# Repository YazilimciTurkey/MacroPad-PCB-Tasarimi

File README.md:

Projeme sponsor oldukları için @PCBWay tekrardan teşekkürler.
PCBWay 10 tanesi 5$ PCB kartlarınızı ürettirebilirsiniz. 
PCBWay size her türlü 3D, CNC, kalıp plastik, ve metal işleme gibi ihtiyaçlarınızı karşılar. 
PCBWay: https://www.pcbway.com/
Tasarım Dosyaları: Yapımda!!
PCBWay detaylı sipariş verme videosu: Yakında!!!
Daha fazla projem için: 
Hackster.io profilim: https://www.hackster.io/hamzadenizyilmaz
#pcbway #pcb #pcbuild 
English/İngilizce
Thanks again @PCBWay for sponsoring my project.
PCBWay You can have your PCB boards produced for 10$. And it provides all kinds of printing and assembly services.
PCBWay: https://www.pcbway.com/
Design Files: Under Construction!!
For more of my projects:
My Hackster.io profile: https://www.hackster.io/hamzadenizyilmaz
#pcbway #pcb #pcbuild #pcbtoday
Videom:https://youtu.be/eG-ILG9O8ic
My video: https://youtu.be/eG-ILG9O8ic

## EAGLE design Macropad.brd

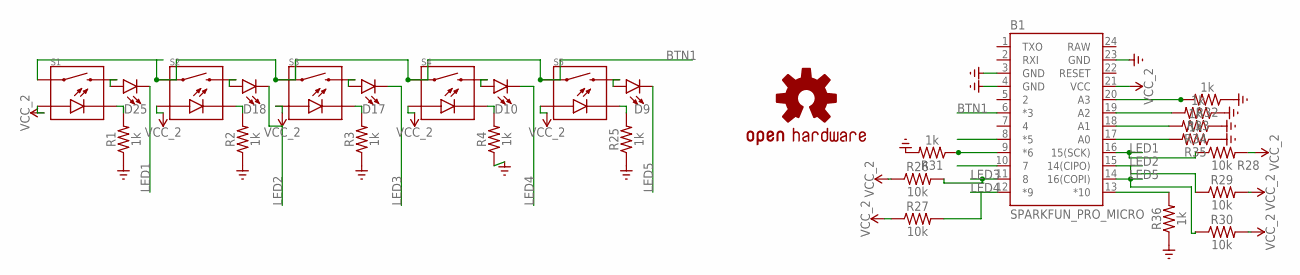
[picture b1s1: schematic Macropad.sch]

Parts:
B1: SPARKFUN_PRO_MICRO
D9, D10, D17, D18, D25: LED3MM; LED_3MM
LOGO1: OSHW-LOGOM-COPPER; OSHW-LOGO-M_COPPER
R1, R2, R3, R4, R25, R31, R32, R33, R34, R35, R36: 1k; AXIAL-0.3
R26, R27, R28, R29, R30: 10k; AXIAL-0.3
S1, S2, S3, S4, S5: 1POLE-FIXPINS-W/LED; 1POLE-FIXPINS-W/LED-EASYSOLDER

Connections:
BTN1: B1.6 (*3), S1.1, S2.1, S3.1, S4.1, S5.1
GND: B1.3 (GND), B1.4 (GND), B1.23 (GND), R1.P$1 (1), R2.P$1 (1), R3.P$1 (1), R4.P$1 (1), R25.P$1 (1), R31.P$2 (2), R32.P$1 (1), R33.P$1 (1), R34.P$1 (1), R35.P$1 (1), R36.P$1 (1)
LED1: B1.16 (15(SCK)), D25.K (C), R28.P$1 (1)
LED2: B1.15 (14(CIPO)), D18.K (C), R29.P$1 (1)
LED3: B1.11 (8), D17.K (C), R26.P$2 (2)
LED4: B1.12 (*9), D10.K (C), R27.P$2 (2)
LED5: B1.14 (16(COPI)), D9.K (C), R30.P$1 (1)
unnamed: R1.P$2 (2), S1.4
unnamed: R2.P$2 (2), S2.4
unnamed: R3.P$2 (2), S3.4
unnamed: R4.P$2 (2), S4.4
unnamed: R25.P$2 (2), S5.4
unnamed: D25.A, S1.2
unnamed: D18.A, S2.2
unnamed: D17.A, S3.2
unnamed: D10.A, S4.2
unnamed: D9.A, S5.2
unnamed: B1.9 (*6), R31.P$1 (1)
unnamed: B1.20 (A3), R32.P$2 (2)
unnamed: B1.19 (A2), R33.P$2 (2)
unnamed: B1.18 (A1), R34.P$2 (2)
unnamed: B1.17 (A0), R35.P$2 (2)
unnamed: B1.13 (*10), R36.P$2 (2)
NET,: B1.8 (*5)
RAW: B1.24 (RAW)
VCC_2: B1.21 (VCC), R26.P$1 (1), R27.P$1 (1), R28.P$2 (2), R29.P$2 (2), R30.P$2 (2), S1.3, S2.3, S3.3, S4.3, S5.3

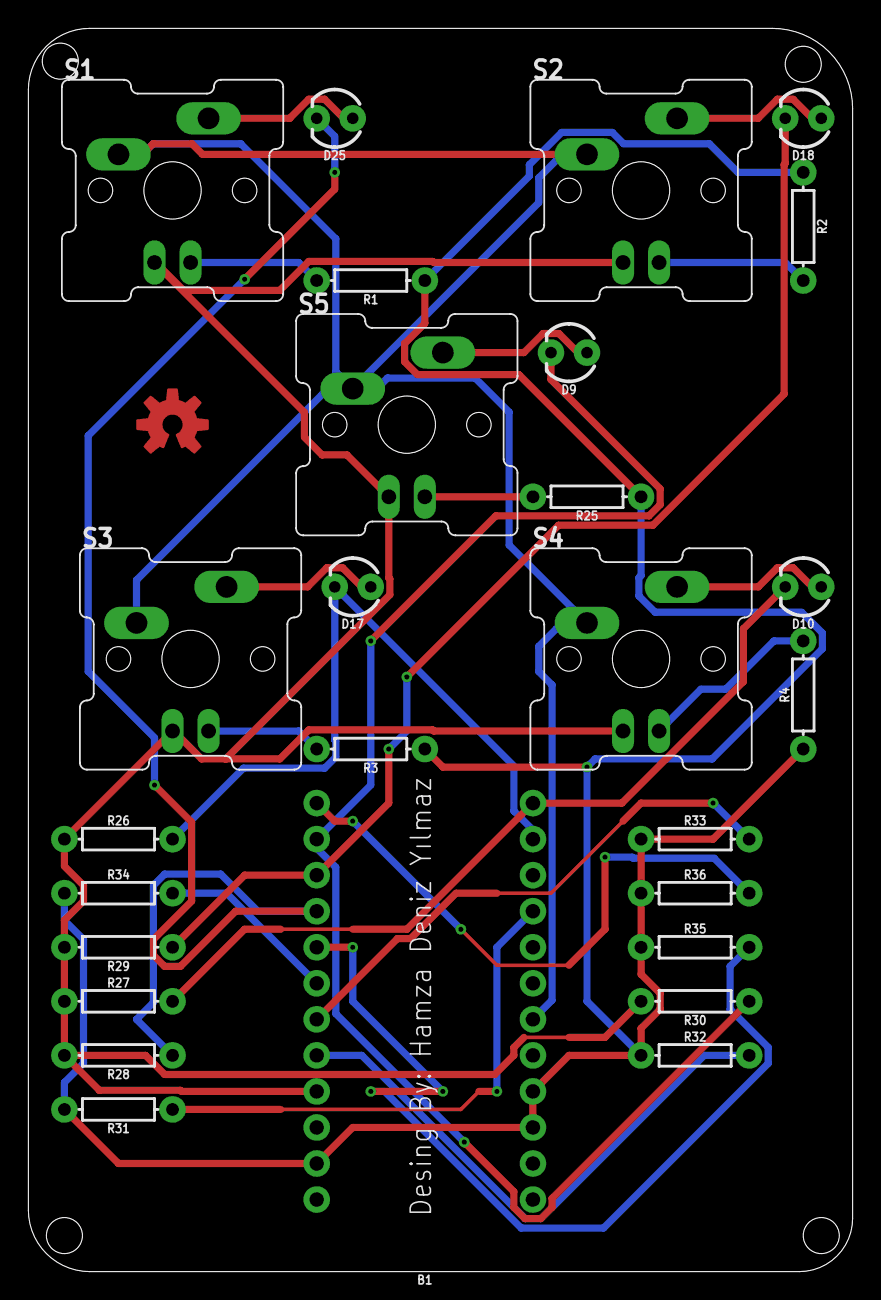
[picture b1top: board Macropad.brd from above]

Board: 2 copper layers, 58.1 x 87.6 mm, 28 parts (0 on the bottom side), 24 nets.

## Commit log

2023-01-13 Macropad.brd
    Macropad.brd
2023-01-13 Macropad.sch
    Macropad.sch

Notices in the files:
parts and their libraries:
SparkFun-Boards: Licensing: Creative Commons ShareAlike 4.0 International - https://creativecommons.org/licenses/by-sa/4.0
